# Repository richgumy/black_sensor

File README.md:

# Soft Surface Pressure Sensor using EIT
Black sensor is a project aimed at characterising carbon black silicone composites (and other piezoresistive conductive particle elastomer composites). This material can also be used as a pressure sensitive skin. The sensor system uses the principle of electrical impedance tomography (EIT) to reconstruct a resisitivty map of a flat sheet of piezoresisitive composite (characteristic limits of material yet to be determined. Such as min/max inter-electrode resisitvity and gauge factor) We will be only using DC as we are solely interested in the resisitive qualities of the composite for now, hence we're using electrical resistivity tomography (ERT). The sensor has been created that contains 4 major parts:

1) [ERT PCB hardware](/README.md#1---ert-pcb-hardware)
2) [ERT PCB firmware](/README.md#2---ert-pcb-firmware)
3) [Reconstruction software](/README.md#3---reconstruction-software)
4) [Sensor domain parts](/README.md#4---sensor-domain-parts)

A low cost PCB has been developed to capture the ERT data in reatime, which is streamed to a another computer to run a resistivity image reconstruction algorithm.

## 1 - ERT PCB hardware
The hardware driving the ERT sensor consist of either one custom ERT PCB or a MUX PCB used with an ESP32 development board and source measurement unit (SMU). All of the files to create the hardware are given as raw KiCad files. All of the component libraries may not exist so will need to made manually or imported.
[SMU PCB pinout here](/pcb-firmware/pcb_mux/README.md)
### 2.1 - ERT PCB
This board is for ERT data collection limited to sensor domains which have lower resisitances throughout the entirety of its intended use. The adjacent electrode resistance must not exceeed approx. 5 $k\Omega$.
#### Features:
- 5v USB power supply
- Onboard USB-UART programming
- Four 16:1 SPI MUXs
- Trimpot controlled current source
- Trimpot controlled voltage measurement gain
- 16 bit SPI ADC
- WiFi/BT capability
#### Future Features:
- Impedance measurements using network analyser
- Smaller PCB size
- Lower power MCU
### 2.2 - MUX PCB
This system consists of a SPI controlled 4:16 multiplexer (MUX) PCB used controlled with an ESP32 development board, PC and driven by a Keithley 2634b SMU and Keithley 2230G-30-1 DC power supply.
#### Features:
- Onboard USB-UART programming
- Four 16:1 SPI MUXs
- WiFi/BT capability
#### Future Features:
- Miniatruise and move all this system's functionality to the ERT PCB

## 2 - ERT PCB firmware
To run a test with the Cartesian force applicator see instructions in directory [here](pcb-firmware/pcb_mux/README.md)

### 2.1 - ERT PCB
The PCB firmware is all written in C for the ESP32-WROOM SoC connected to a custom 'ERT PCB'. The firmware applies an electrode pattern to the electrodes and sends measurement data via the USB UART serial connection.
The basic electrode drive process is:
1. Apply current to 2 electrodes
2. Measure voltage across 16 electrode pairs
3. Send voltage measurement data via serial
4. Iterate to next set of current electrodes.
5. Back to step 1.
#### Features:
- Drive modes: Standby, Calibrate, Adjacent
- Measurement averaging
- 16bit analog reading
#### Future Features:
- Bluetooth transmission of serial data
- More drive modes: Pseudo polar, PP-PP
- Nonense data checker (Throw error if data is very noisy or ADC saturated etc.)
- Speed up measurement rate from 8Hz to 40Hz

### 2.2 - MUX PCB - ESP32/PC
This is a more modular approach so that we are not limited by the ERT PCB's current source and power supply values. This system has five main components: A Keithley 2634b SMU, a MUX PCB, an ESP32 WROOM32 development board, a Keithley 2230G-30-1 DC power supply, and a piezoresistive sensor domain. The whole system is controlled via the PCB connected to the ESP32 and SMU over UART. 
The basic electrode drive process is:
1. Apply current to 2 electrodes
2. Measure voltage across 16 electrode pairs
3. Send voltage measurement data via serial
4. Iterate to next set of current electrodes.
5. Back to step 1.

These steps are done using a PC to send commands for switching the MUC PCB and query messages sent to the SMU to get voltage and current values.

#### Features:
- Simple serial control
- Voltage measurement time integration
- Nonense data checker (Throw error if SMU Isrc voltage saturating or DC power supply saturating)
- Logs the electrode resistance at beginning of cycle

#### Future Features:
- More drive modes: Pseudo polar, PP-PP
- Speed up measurement rate from 0.3Hz to ??Hz

## 3 - Reconstruction software
EIDORS was used as the library for image reconstruction using the data gathered from the PCB. A reference measurement is taken from the material on start-up of the reconstruction program. The reference measurement is compared to a current measurement for change in resisitvity (\Delta R) image reconstruction.

### Features:
- Reconstructs image in realtime using serial data.
- Save images for video generation
- See EIDORS documentation for an extensive feature list: http://eidors3d.sourceforge.net/index.shtml
- Timestamped FEM and measurement data exported to .pkl files.

### Future Features:
- Optimise reconstruction by porting all functionality to C++ or for use with a TPU/GPU.

## 4 - Sensor domain mechanical parts
The rest of the physical system consists of:
1. Composite material under test (MUT)
2. MUT holder
3. MUT electrodes
The material we are using is a carbon black nanoparticle silicone rubber composite, with customisable properties depending on the fabrication process. The MUT holder is a 3D printed part that provides an ideal platform for the material to be tested on. The MUT electrodes maintain a reliable connection between the MUT and the ERT PCB.
### Features:
- 100mm diameter pressure test area
- Easily customisable for other MUT sizes and MUT materials within measurement range.
### Future Features:
- Standard test domains and MUT holder/electrode configurations

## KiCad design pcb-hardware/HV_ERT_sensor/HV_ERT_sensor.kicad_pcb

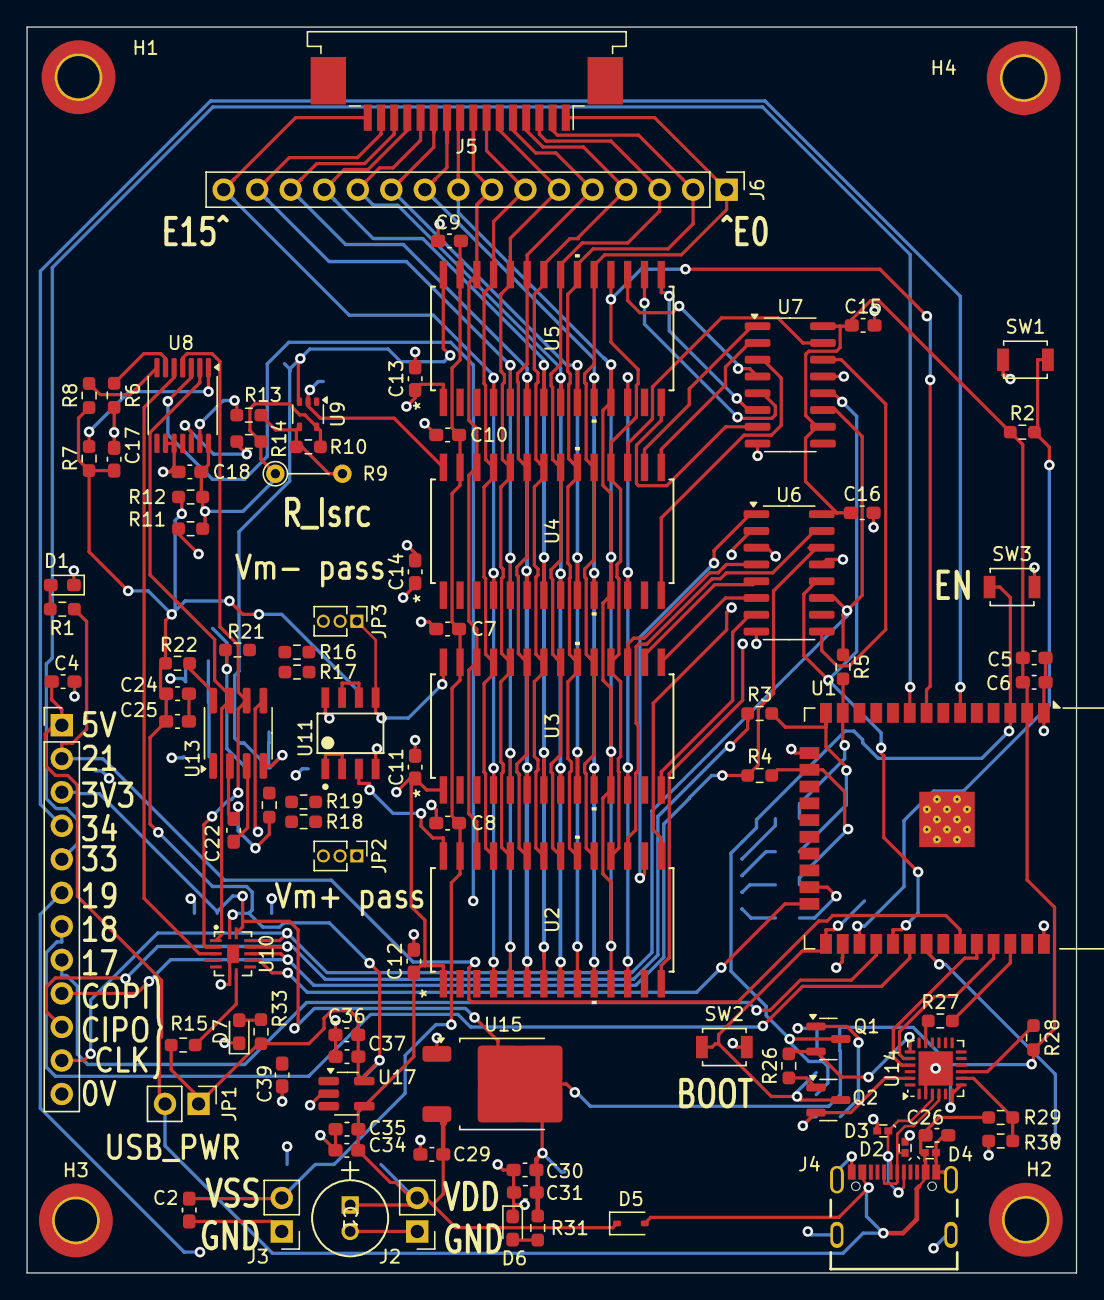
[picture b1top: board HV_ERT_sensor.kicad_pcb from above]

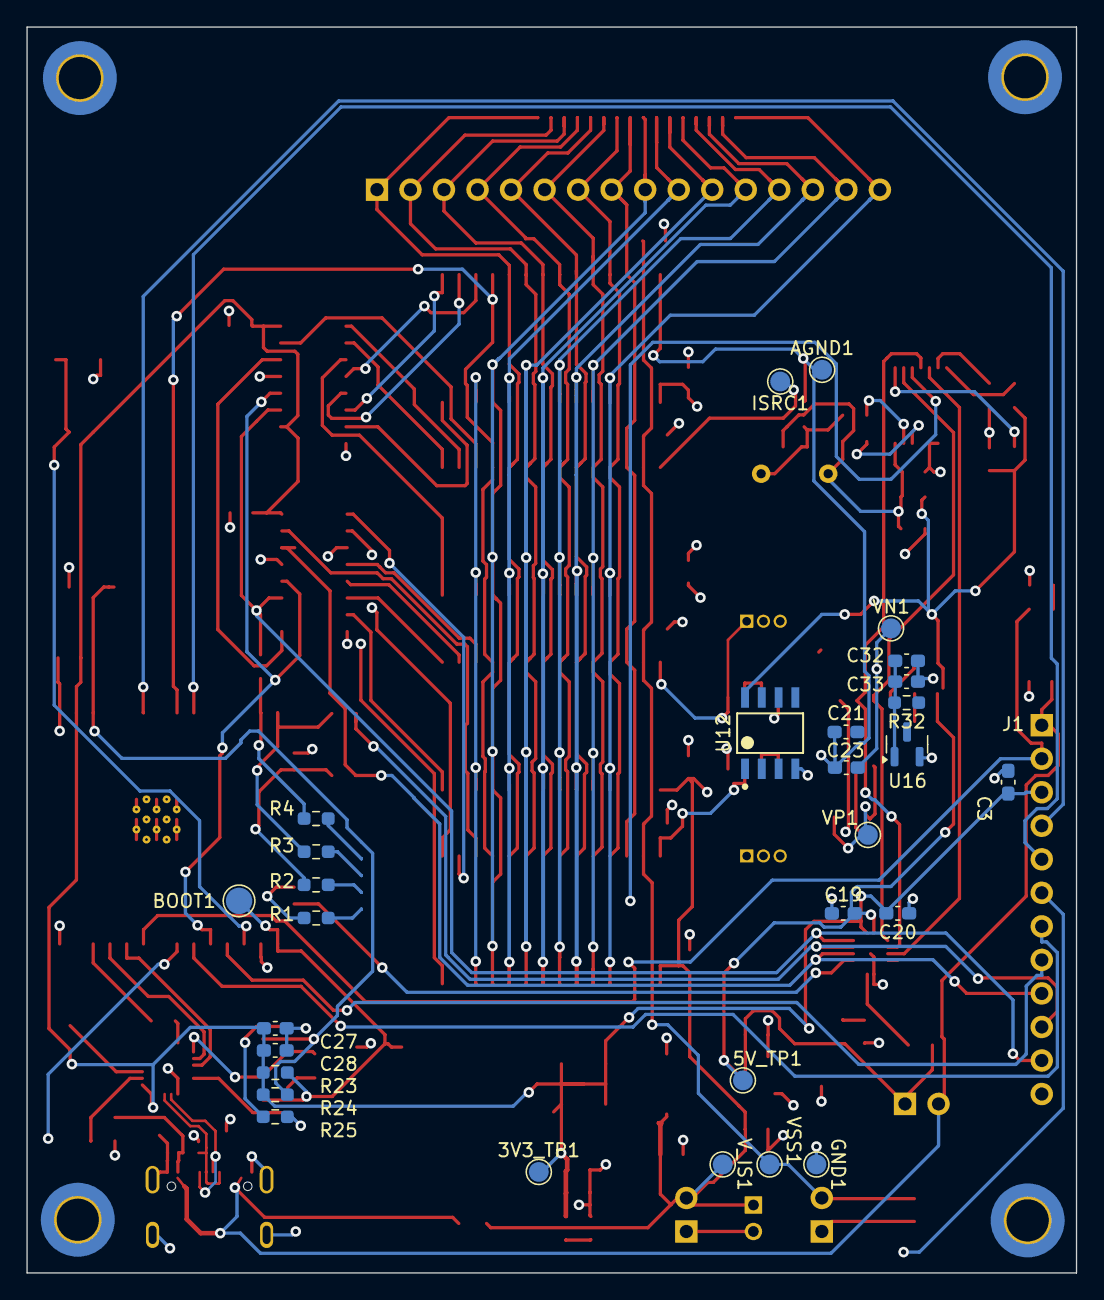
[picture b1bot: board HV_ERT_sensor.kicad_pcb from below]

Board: 4 copper layers, 79.5 x 94.4 mm, 127 parts (29 on the bottom side), 101 nets.

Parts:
3V3_TP1, 5V_TP1: TestPoint; TestPoint_Pad_D1.5mm
AGND1: TestPoint; TestPoint_Pad_D1.5mm
BOOT1: TP_s; TestPoint_Pad_D2.0mm
C1: C_Polarized; CAP_PAN_5X11_PAN
C2, C5, C24, C33, C37: 1u; C_0603_1608Metric_Pad1.08x0.95mm_HandSolder
C3, C4, C6, C7, C8, C9, C10, C11, C12, C13, C14, C15, C16, C17, C18, C19, C20, C25, C28, C30, C32, C35, C39: 100n; C_0603_1608Metric_Pad1.08x0.95mm_HandSolder
C21, C23: 1n; C_0603_1608Metric_Pad1.08x0.95mm_HandSolder
C22: 10n; C_0603_1608Metric_Pad1.08x0.95mm_HandSolder
C26, C29, C31: 10u; C_0603_1608Metric_Pad1.08x0.95mm_HandSolder
C27: 4u7; C_0603_1608Metric_Pad1.08x0.95mm_HandSolder
C34, C36: 470n; C_0603_1608Metric_Pad1.08x0.95mm_HandSolder
D1, D6, D7: 150060VS75000; LED_0603_1608Metric_Pad1.05x0.95mm_HandSolder
D2, D3, D4: UAD8C05L01; D_SOD-882
D5: BAT760-7; D_SOD-323
GND1: TestPoint; TestPoint_Pad_D1.5mm
H1, H2, H3, H4: MountingHole_Pad; MountingHole_3.2mm_M3_DIN965_Pad_TopBottom
ISRC1: TestPoint; TestPoint_Pad_D1.5mm
J1: Conn_01x12_Pin; PinHeader_1x12_P2.54mm_Vertical
J2, J3: Conn_01x02_Male; PinHeader_1x02_P2.54mm_Vertical
J4: USB_C_HEADER; GCT_USB4105-GF-A
J5: Conn_01x16; TE_1-84952-6_1x16-1MP_P1.0mm_Horizontal
J6: Conn_01x16; PinHeader_1x16_P2.54mm_Vertical
JP1: Jumper_2_Open; PinHeader_1x02_P2.54mm_Vertical
JP2, JP3: Jumper_3_Open; PinHeader_1x03_P1.27mm_Vertical
Q1, Q2: BC848; SOT-23
R1, R1#2, R2#2, R3#2, R4#2, R20, R21, R31: 100R; R_0603_1608Metric_Pad0.98x0.95mm_HandSolder
R2, R6, R8, R15, R23, R24, R25, R26, R28, R32: 10k; R_0603_1608Metric_Pad0.98x0.95mm_HandSolder
R3, R4, R5: 68R; R_0603_1608Metric_Pad0.98x0.95mm_HandSolder
R7, R11, R12, R13, R14, R22: 0R; R_0603_1608Metric_Pad0.98x0.95mm_HandSolder
R9: 0R; R_Axial_DIN0204_L3.6mm_D1.6mm_P5.08mm_Vertical
R10: 680R; R_0603_1608Metric_Pad0.98x0.95mm_HandSolder
R16, R18: 3k3 1%; R_0603_1608Metric_Pad0.98x0.95mm_HandSolder
R17, R19: 1k 1%; R_0603_1608Metric_Pad0.98x0.95mm_HandSolder
R27: 10K; R_0603_1608Metric_Pad0.98x0.95mm_HandSolder
R29: 22K; R_0603_1608Metric_Pad0.98x0.95mm_HandSolder
R30: 47K; R_0603_1608Metric_Pad0.98x0.95mm_HandSolder
R33: 200R; R_0603_1608Metric_Pad0.98x0.95mm_HandSolder
SW1: PTS636; SW_SPST_B3U-1000P
SW2, SW3: PTS636 SM50 SMTR LFS; SW_SPST_B3U-1000P
U1: ESP32-WROOM-32
U2, U3, U4, U5: DG406DYZ; SOIC28_7P60X18P10_INR-M
U6, U7: SN74HC595; SOIC-16_3.9x9.9mm_P1.27mm
U8: MCP41HV51-103E/ST; TSSOP-14_4.4x5mm_P0.65mm
U9: PSSI2021SAY; SOT-353_SC-70-5
U10: NTS0104BQ; DHVQFN14-2.5x3
U11, U12: OPA2991IDR; D0008A-MFG
U13: LTC1864; SOIC-8_3.9x4.9mm_P1.27mm
U14: CP2102N-A01-GQFN24; QFN-24-1EP_4x4mm_P0.5mm_EP2.6x2.6mm
U15: LD1086DT33TR; TO-252-2
U16: ADR5045BRTZ; SOT-23
U17: LDK715M50R_SOT23-5; SOT-23-5_HandSoldering
VN1: TestPoint; TestPoint_Pad_D1.5mm
VP1: TestPoint; TestPoint_Pad_D1.5mm
VSS1: TestPoint; TestPoint_Pad_D1.5mm
V_IS1: TestPoint; TestPoint_Pad_D1.5mm

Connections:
5V_USB: C4.2, C26.1, D4.1 (A1), D5.2 (A), J1.1, J4.A4_B9 (VBUS), J4.B4_A9 (VBUS), JP1.2 (B), R29.1
+3V3: 3V3_TP1.1, C3.2, C5.1, C6.1, C15.1, C16.1, C20.2, C27.1, C28.1, C30.2, C31.1, J1.3, R2.1, R23.1, R24.1, R28.2, R31.1, U1.2 (VDD), U6.10 (~SRCLR), U6.16 (VCC), U7.10 (~SRCLR), U7.16 (VCC), U10.14 (VCCB), U14.6 (VDD), U14.7 (REGIN), U15.2 (OUT)
+5V: 5V_TP1.1, C17.2, C19.2, C24.1, C25.2, C36.2, C37.1, JP1.1 (A), R7.1, R8.1, R12.1, R15.2, R22.2, R33.1, U10.1 (VCCA), U12.8 (V+), U17.5 (OUT)
/ADC_CS: U1.24 (IO2), U10.10 (B4)
/BOOT: BOOT1.1, Q2.3 (C), R23.2, SW2.1, U1.25 (IO0)
/DIGPOT_CS: U1.26 (IO4), U8.3 (*CS)
/EN: Q1.3 (C), R24.2, SW3.1, U1.3 (EN)
/IO15_SW: R2.2, SW1.2, U1.27 (IO16)
/IO17: J1.8, U1.28 (IO17)
/IO18: J1.7, U1.30 (IO18)
/IO19: J1.6, U1.31 (IO19)
/IO21_LED: J1.2, R1.1, U1.33 (IO21)
/IO33: J1.5, U1.9 (IO33)
/IO34: J1.4, U1.6 (IO34)
/Isrc: ISRC1.1, U4.28 (D), U9.2
/MTCLK: R2#2.1, R4.2, U1.16 (IO13)
/MTDI: R3.2, R3#2.1, U1.14 (IO12)
/MTDO: R1#2.1, U1.23 (IO15)
/MTMS: R4#2.1, R5.2, U1.13 (IO14)
/MUX_CS: U1.29 (IO5), U6.12 (RCLK), U7.12 (RCLK)
/MUX_EN: U1.8 (IO32), U2.18 (EN), U3.18 (EN), U4.18 (EN), U5.18 (EN)
/RXD: U1.35 (TXD0/IO1), U14.20 (RXD)
/SPICIPO: J1.10, R3.1, U10.12 (B2)
/SPICLK: J1.11, R5.1, U6.11 (SRCLK), U7.11 (SRCLK), U10.13 (B1)
/SPICOPI: J1.9, R4.1, U6.14 (SER), U10.11 (B3)
/TXD: U1.34 (RXD0/IO3), U14.21 (TXD)
/USB_DN: D2.1 (A1), J4.A7 (DN1), J4.B7 (DN2), U14.4 (D-)
/USB_DP: D3.1 (A1), J4.A6 (DP1), J4.B6 (DP2), U14.3 (D+)
/USB_SUSP: R27.2, U1.36 (IO22)
/Vmeas+: JP2.1 (A), U2.28 (D), U11.3 (IN1+)
/Vmeas-: JP3.1 (A), U3.28 (D), U11.5 (IN2+)
/eit_drv/ADC_CS5V: U10.5 (A4), U13.5 (CONV)
/eit_drv/R_IS1: C18.1, R9.1, R10.1, R11.2, R12.2, R14.1, U8.14 (V+), U9.5
/eit_drv/R_IS2: R9.2, R10.2, R13.2, U9.4
/eit_drv/SPICIPO5V: U8.4 (SDI), U10.3 (A2), U13.6 (SDO)
/eit_drv/SPICLK5V: U8.2 (SCK), U10.2 (A1), U13.7 (SCK)
/eit_drv/SPICOPI5V: U8.5 (SDO), U10.4 (A3)
/eit_drv/Vmeas+_ADC: JP2.2 (C), R20.1
/eit_drv/Vmeas+_Op: JP2.3 (B), U12.1 (OUT1), U12.2 (IN1-)
/eit_drv/Vmeas-_ADC: JP3.2 (C), R21.1
/eit_drv/Vmeas-_Op: JP3.3 (B), U12.6 (IN2-), U12.7 (OUT2)
/mux_4-16/S0_A: U2.17 (A0), U6.15 (QA)
/mux_4-16/S0_B: U3.17 (A0), U6.4 (QE)
/mux_4-16/S1_A: U2.16 (A1), U6.1 (QB)
/mux_4-16/S1_B: U3.16 (A1), U6.5 (QF)
/mux_4-16/S2_A: U2.15 (A2), U6.2 (QC)
/mux_4-16/S2_B: U3.15 (A2), U6.6 (QG)
/mux_4-16/S3_A: U2.14 (A3), U6.3 (QD)
/mux_4-16/S3_B: U3.14 (A3), U6.7 (QH)
/mux_4-16/S4_A: U4.17 (A0), U7.15 (QA)
/mux_4-16/S4_B: U5.17 (A0), U7.4 (QE)
/mux_4-16/S5_A: U4.16 (A1), U7.1 (QB)
/mux_4-16/S5_B: U5.16 (A1), U7.5 (QF)
/mux_4-16/S6_A: U4.15 (A2), U7.2 (QC)
/mux_4-16/S6_B: U5.15 (A2), U7.6 (QG)
/mux_4-16/S7_A: U4.14 (A3), U7.3 (QD)
/mux_4-16/S7_B: U5.14 (A3), U7.7 (QH)
/power/5V_REF: C32.2, C33.1, R32.2, U16.1 (V+)
/usb2uart/DTR: Q2.2 (E), R25.2, U14.23 (DTR)
/usb2uart/RTS: Q1.2 (E), R26.2, U14.19 (RTS)
/usb2uart/VBUS_UART: R29.2, R30.1, U14.8 (VBUS)
E0: J5.1, J6.1, U2.19 (S1), U3.19 (S1), U4.19 (S1), U5.19 (S1)
E1: J5.2, J6.2, U2.20 (S2), U3.20 (S2), U4.20 (S2), U5.20 (S2)
E2: J5.3, J6.3, U2.21 (S3), U3.21 (S3), U4.21 (S3), U5.21 (S3)
E3: J5.4, J6.4, U2.22 (S4), U3.22 (S4), U4.22 (S4), U5.22 (S4)
E4: J5.5, J6.5, U2.23 (S5), U3.23 (S5), U4.23 (S5), U5.23 (S5)
E5: J5.6, J6.6, U2.24 (S6), U3.24 (S6), U4.24 (S6), U5.24 (S6)
E6: J5.7, J6.7, U2.25 (S7), U3.25 (S7), U4.25 (S7), U5.25 (S7)
E7: J5.8, J6.8, U2.26 (S8), U3.26 (S8), U4.26 (S8), U5.26 (S8)
E8: J5.9, J6.9, U2.11 (S9), U3.11 (S9), U4.11 (S9), U5.11 (S9)
E9: J5.10, J6.10, U2.10 (S10), U3.10 (S10), U4.10 (S10), U5.10 (S10)
E10: J5.11, J6.11, U2.9 (S11), U3.9 (S11), U4.9 (S11), U5.9 (S11)
E11: J5.12, J6.12, U2.8 (S12), U3.8 (S12), U4.8 (S12), U5.8 (S12)
E12: J5.13, J6.13, U2.7 (S13), U3.7 (S13), U4.7 (S13), U5.7 (S13)
E13: J5.14, J6.14, U2.6 (S14), U3.6 (S14), U4.6 (S14), U5.6 (S14)
E14: J5.15, J6.15, U2.5 (S15), U3.5 (S15), U4.5 (S15), U5.5 (S15)
E15: J5.16, J6.16, U2.4 (S16), U3.4 (S16), U4.4 (S16), U5.4 (S16)
GND: AGND1.1, C1.2, C2.2, C3.1, C4.1, C5.2, C6.2, C7.2, C8.2, C9.2, C10.2, C11.2, C12.2, C13.2, C14.2, C15.2, C16.2, C17.1, C18.2, C19.1, C20.1, C21.1, C23.1, C24.2, C25.1, C26.2, C27.2, C28.2, C29.2, C30.1, C31.2, C32.1, C33.2, C34.2, C35.2, C36.1, C37.2, C39.2, D1.1 (K), D2.2 (A2), D3.2 (A2), D4.2 (A2), D6.1 (K), D7.1 (K), GND1.1, H1.1, H2.1, H3.1, H4.1, J1.12, J2.1, J3.1, J4.A1_B12 (GND), J4.B1_A12 (GND), J4.S1 (SHELL_GND), J4.S2 (SHELL_GND), J4.S3 (SHELL_GND), J4.S4 (SHELL_GND), R6.2, R17.1, R19.1, R30.2, SW1.1, SW2.2, SW3.2, U1.1 (GND), U1.15 (GND), U1.38 (GND), U1.39 (GND), U2.12 (GND), U3.12 (GND), U4.12 (GND), U5.12 (GND), U5.28 (D), U6.8 (GND), U6.13 (~OE), U7.8 (GND), U7.13 (~OE), U8.9 (DGND), U8.10 (V-), U9.3 (GND), U10.7 (GND), U11.4 (V-), U12.4 (V-), U13.4 (GND), U14.2 (GND), U14.25 (GND), U15.1 (ADJ/GND), U16.2 (V-), U17.2 (GND)
unnamed: D1.2 (A), R1.2
unnamed: D6.2 (A), R31.2
unnamed: D7.2 (A), R33.2
unnamed: Q1.1 (B), R25.1
unnamed: Q2.1 (B), R26.1
unnamed: U6.9 (QH'), U7.14 (SER)
unnamed: R8.2, U8.7 (*SHDN)
unnamed: R6.1, U8.6 (*WLAT)
unnamed: R13.1, U8.13 (P0A)
unnamed: R14.2, U8.12 (P0W)
unnamed: R7.2, U8.1 (VL)
unnamed: R15.1, U10.8 (OE)
unnamed: R18.2, U11.1 (OUT1), U11.2 (IN1-)
unnamed: R16.2, U11.6 (IN2-), U11.7 (OUT2)
unnamed: R18.1, R19.2, U12.3 (IN1+)
unnamed: R16.1, R17.2, U12.5 (IN2+)
unnamed: C21.2, C22.2, R20.2, U13.2 (IN+), VP1.1
unnamed: C22.1, C23.2, R21.2, U13.3 (IN-), VN1.1
unnamed: R22.1, U13.8 (VCC)
unnamed: R27.1, U14.17 (SUSPEND)
unnamed: R28.1, U14.9 (~RSTb)
VDD: C1.1, C11.1, C12.1, C13.1, C14.1, C29.1, C34.1, C35.1, D5.1 (K), J2.2, R11.1, R32.1, U2.1 (V+), U3.1 (V+), U4.1 (V+), U5.1 (V+), U11.8 (V+), U15.3 (IN), U17.4 (IN), V_IS1.1
VSS: C2.1, C7.1, C8.1, C9.1, C10.1, J3.2, U2.27 (V-), U3.27 (V-), U4.27 (V-), U5.27 (V-), VSS1.1

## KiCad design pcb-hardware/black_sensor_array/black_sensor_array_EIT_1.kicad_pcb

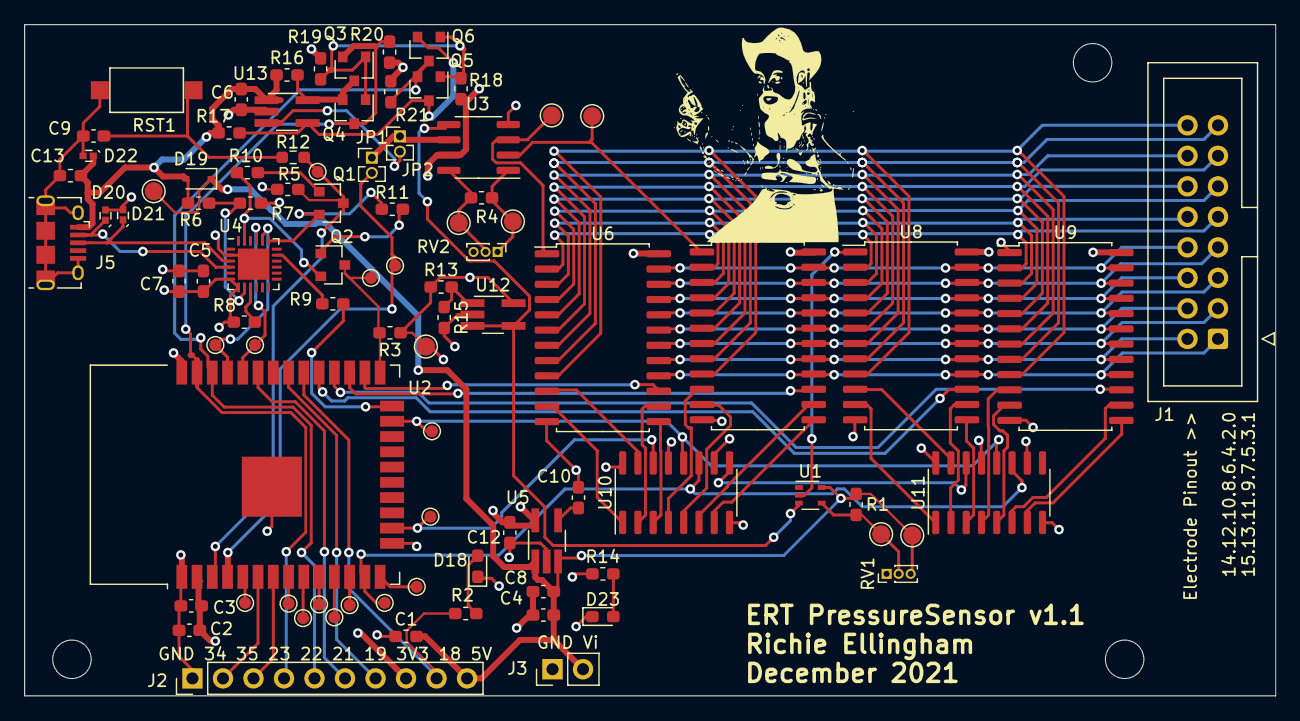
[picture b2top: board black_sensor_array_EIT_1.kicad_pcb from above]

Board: 4 copper layers, 104.1 x 55.9 mm, 93 parts (0 on the bottom side), 90 nets.

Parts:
C1: 100n; C_0603_1608Metric_Pad1.05x0.95mm_HandSolder
C2, C6, C7, C9: 100n; C_0603_1608Metric_Pad1.08x0.95mm_HandSolder
C3, C4, C5: 10u; C_0603_1608Metric_Pad1.08x0.95mm_HandSolder
C8: 1u; C_0603_1608Metric_Pad1.08x0.95mm_HandSolder
C10: 10n; C_0603_1608Metric_Pad1.08x0.95mm_HandSolder
C12: 2.2u; C_0603_1608Metric_Pad1.08x0.95mm_HandSolder
C13: 10u; C_0603_1608Metric_Pad1.05x0.95mm_HandSolder
D18, D23: 150060VS75000; LED_0603_1608Metric_Pad1.05x0.95mm_HandSolder
D19: BAT760-7; D_SOD-323
D20, D21, D22: UAD8C05L01; D_SOD-882
H1, H2, H3: MountingHole; MountingHole_3.2mm_M3
J1: Conn_02x8; IDC-Header_2x08_P2.54mm_Vertical
J2: Conn_01x10_Male; PinHeader_1x10_P2.54mm_Vertical
J3: Conn_01x02_Male; PinHeader_1x02_P2.54mm_Vertical
J5: USB_B_Micro; USB_Micro-B_Amphenol_10118194_Horizontal
JP1, JP2: Jumper; PinHeader_1x02_P1.27mm_Vertical
Q1, Q2, Q3, Q4, Q5, Q6: BC848; SOT-23
R1: 120K; R_0603_1608Metric_Pad1.05x0.95mm_HandSolder
R2, R14: 100R; R_0603_1608Metric_Pad1.05x0.95mm_HandSolder
R3, R5, R8, R10, R11, R13, R15, R16, R17, R18, R19, R20, R21: 10k; R_0603_1608Metric_Pad1.05x0.95mm_HandSolder
R4, R7: 47K; R_0603_1608Metric_Pad1.05x0.95mm_HandSolder
R6: 22K; R_0603_1608Metric_Pad1.05x0.95mm_HandSolder
R9: 10K; R_0603_1608Metric_Pad1.05x0.95mm_HandSolder
R12: 100R; R_0603_1608Metric_Pad0.98x0.95mm_HandSolder
RST1: PTS636 SM50 SMTR LFS; SW_SPST_CK_RS282G05A3
RV1, RV2: R_POT_TRIM; PinHeader_1x03_P1.00mm_Vertical
TP1, TP2, TP8, TP9, TP14, TP15, TP18, TP23: TestPoint; TestPoint_Pad_D1.5mm
TP3, TP4, TP5, TP6, TP7, TP10, TP11, TP12, TP13, TP16, TP17, TP19, TP20, TP21, TP22: TP_s; TestPoint_Pad_D1.0mm
U1: PSSI2021SAY; SOT-353_SC-70-5
U2: ESP32-WROOM-32
U3: INA126; SOIC-8_3.9x4.9mm_P1.27mm
U4: CP2102N-A01-GQFN24; QFN-24-1EP_4x4mm_P0.5mm_EP2.6x2.6mm
U5: CAT6219−330TDGT3; TSOT-23-5_HandSoldering
U6, U7, U8, U9: CD74HC4067M; SOIC-24W_7.5x15.4mm_P1.27mm
U10, U11: SN74HC595; SOIC-16_3.9x9.9mm_P1.27mm
U12: MCP6006UT-E_OT; TSOT-23-5_HandSoldering
U13: MCP3221A7T-E_OT; TSOT-23-5_HandSoldering

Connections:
+3V3: C2.1, C3.1, C5.1, C7.1, C12.1, J2.8, R3.1, R5.1, R8.2, R13.1, R14.1, R18.1, R19.1, R20.1, R21.1, TP23.1, U2.2, U3.7, U4.6, U4.7, U5.5, U6.24, U7.24, U8.24, U9.24, U10.10, U10.16, U11.10, U11.16, U12.5
/3v3_PU: Q3.1, Q4.1, Q5.1, Q6.1, R18.2, R19.2
/5VBUS: C6.1, C13.1, D19.2, D22.1, J5.1, R6.1, R16.1, R17.1, U13.1
/5V_USB: C1.2, C4.2, C8.1, D19.1, J2.10, J3.2, R1.1, RV1.3, TP1.1, TP18.1, U1.5, U5.1, U5.3
/ADC_jump: JP1.1, JP2.1, U3.6
/ADC_jump_ex: JP2.2, U13.3
/ADC_jump_int: JP1.2, TP16.1, U2.4
/DTR: Q2.2, R10.2, U4.23
/DTR*: Q2.3, R3.2, TP22.1, U2.25
/E0x: J1.16, U6.9, U7.9, U8.9, U9.9
/E1x: J1.15, U6.8, U7.8, U8.8, U9.8
/E2x: J1.14, U6.7, U7.7, U8.7, U9.7
/E3x: J1.13, U6.6, U7.6, U8.6, U9.6
/E4x: J1.12, U6.5, U7.5, U8.5, U9.5
/E5x: J1.11, U6.4, U7.4, U8.4, U9.4
/E6x: J1.10, U6.3, U7.3, U8.3, U9.3
/E7x: J1.9, U6.2, U7.2, U8.2, U9.2
/E8x: J1.8, U6.23, U7.23, U8.23, U9.23
/E9x: J1.7, U6.22, U7.22, U8.22, U9.22
/E10x: J1.6, U6.21, U7.21, U8.21, U9.21
/E11x: J1.5, U6.20, U7.20, U8.20, U9.20
/E12x: J1.4, U6.19, U7.19, U8.19, U9.19
/E13x: J1.3, U6.18, U7.18, U8.18, U9.18
/E14x: J1.2, U6.17, U7.17, U8.17, U9.17
/E15x: J1.1, U6.16, U7.16, U8.16, U9.16
/EN_GND: U2.28, U9.15
/EN_Isrc: U2.29, U8.15
/EN_Vmeas+: U2.26, U6.15
/EN_Vmeas-: U2.27, U7.15
/HSPICLK: TP12.1, U2.13, U10.11, U11.11
/HSPICS0: TP13.1, U2.23, U10.12, U11.12
/HSPIMISO: TP10.1, U2.14
/HSPIMOSI: TP11.1, U2.16, U10.14
/IO18_LED: J2.9, R2.1, U2.30
/IO19: J2.7, U2.31
/IO21: J2.6, U2.33
/IO34: J2.2, U2.6
/IO35: J2.3, U2.7
/Isrc: U1.2, U8.1
/MUX_16to4/S0_A: U6.10, U10.15
/MUX_16to4/S0_B: U7.10, U10.4
/MUX_16to4/S1_A: U6.11, U10.1
/MUX_16to4/S1_B: U7.11, U10.5
/MUX_16to4/S2_A: U6.14, U10.2
/MUX_16to4/S2_B: U7.14, U10.6
/MUX_16to4/S3_A: U6.13, U10.3
/MUX_16to4/S3_B: U7.13, U10.7
/MUX_16to4/S4_A: U8.10, U11.15
/MUX_16to4/S4_B: U9.10, U11.4
/MUX_16to4/S5_A: U8.11, U11.1
/MUX_16to4/S5_B: U9.11, U11.5
/MUX_16to4/S6_A: U8.14, U11.2
/MUX_16to4/S6_B: U9.14, U11.6
/MUX_16to4/S7_A: U8.13, U11.3
/MUX_16to4/S7_B: U9.13, U11.7
/RTS: Q1.2, R11.2, U4.19
/RTS*: Q1.3, R5.2, R12.1, TP21.1, U2.3
/RXD: TP19.1, U2.35, U4.20
/SCL_ADC: Q3.3, Q4.2, R16.2, U13.5
/SCL_ADC_3V3: J2.4, Q3.2, Q4.3, R20.2, U2.37
/SDA_ADC: Q5.3, Q6.2, R17.2, U13.4
/SDA_ADC_3V3: J2.5, Q5.2, Q6.3, R21.2, U2.36
/TXD: TP20.1, U2.34, U4.21
/USB_DN: D20.1, J5.2, U4.4
/USB_DP: D21.1, J5.3, U4.3
/USB_SUSP: R9.2, U2.24
/VBUS_UART: R6.2, R7.1, U4.8
/V_GND: U1.3, U3.5, U12.3, U12.4
/Vmeas+: TP8.1, U3.3, U6.1
/Vmeas-: TP9.1, U3.2, U7.1
GND: C1.1, C2.2, C3.2, C4.1, C5.2, C6.2, C7.2, C8.2, C9.2, C10.2, C12.2, C13.2, D18.1, D20.2, D21.2, D22.2, D23.1, J2.1, J3.1, J5.5, J5.6, R7.2, R15.2, RST1.2, U2.1, U2.15, U2.38, U2.39, U3.4, U4.2, U4.25, U5.2, U6.12, U7.12, U8.12, U9.1, U9.12, U10.8, U10.13, U11.8, U11.13, U12.2, U13.2
unnamed: C9.1, R12.2, RST1.1
unnamed: C10.1, U5.4
unnamed: D18.2, R2.2
unnamed: D23.2, R14.2
unnamed: Q1.1, R10.1
unnamed: Q2.1, R11.1
unnamed: R1.2, RV1.2, TP2.1, U1.4
unnamed: R4.1, RV2.1, TP14.1, U3.1
unnamed: R4.2, RV2.2, TP15.1, U3.8
unnamed: R8.1, U4.9
unnamed: R9.1, U4.17
unnamed: R13.2, R15.1, U12.1
unnamed: TP3.1, U2.10
unnamed: TP4.1, U2.11
unnamed: TP5.1, U2.12
unnamed: TP6.1, U2.8
unnamed: TP7.1, U2.9
unnamed: TP17.1, U2.5
unnamed: U10.9, U11.14

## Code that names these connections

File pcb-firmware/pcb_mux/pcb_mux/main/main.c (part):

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#define SW_2 15

// MUX
#define MUX_EN 32
#define MUX_CS_PIN 5

#define GPIO_OUTPUT_PIN_SEL  ((1ULL<<LED) | (1ULL<<MUX_EN))
#define GPIO_INPUT_PIN_SEL  ((1ULL<<SW_1) | (1ULL<<SW_2))

// ADC
#define ADC_CS_PIN 27
#define N_ADC_SAMPLES 1         // set ADC averaging buffer size

// Digipot
#define DIGPOT_CS 4

// Electrodes
static int8_t cycle_dir = 1; // Increment through electrode values (0 is decrement)
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
uint32_t conv_adc_readingLTC1864L(uint8_t data[]) {
    // Converts arbitrary analogue unit to readable mV value
    // uint32_t conv_offset = 0;//32533; // Calibrate for each board (i.e. V_GND)
    // uint32_t conv_scale = 65536;
    uint32_t conv_data = 0;

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{
    uint32_t spi_read = 0;
    uint32_t spi_read_avg = 0;
    // send_spi_cmd(spi_read_ADC, ADC_CS_PIN); // Discard ADC reading from previous cycle
    for (int i = 0; i < N_ADC_SAMPLES; i++) {
        send_spi_cmd(spi_read_ADC, ADC_CS_PIN); // Send SPI cmd to read ADC and store value in 'spi_read_ADC'
        spi_read = conv_adc_readingLTC1864L(spi_read_ADC);
        spi_read_avg += spi_read;
    }
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
    //Configure GPIO
    setup_all_gpio();
    gpio_set_level(MUX_EN, 1);

    ////// UART SPECIFIC CODE ////
    uart_config_t uart_config = {
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                v_read.vn_elec = vn_elec;

                 // Send SPI mux cmd
                send_spi_cmd(elec_index, MUX_CS_PIN);
           
                // ADC SPI read
                int32_t spi_read_avg = (int32_t)read_ADC(spi_read_ADC_buf);
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
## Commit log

2021-07-06 First commit adding code for a cycling through 3 pairs of electrodes, reading their voltage values via the nano's ADC and converting this to a resistance value.
2021-07-06 Added readme
2021-09-10 Added a program which gives the creates material square domain with surrounding electrodes. Finds the electric field for a dipole (current source of two electrodes) and working on creating equipotent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
2021-11-23 added functioning mux changing code for ESP32 based board and 4 muxes
2021-11-23 generalised readme
2021-11-25 calibration sequence added
2022-01-12 Fixing SPI crash with error
2022-01-12 fixed SPI crash bug by adding memset for bus_config...
2022-01-12 fixed ADJACENT electrode drive pattern bug
2022-01-25 added I2C ADC
2022-01-25 I2C ADC teething issues
2022-01-31 Added 24bit ADC SPI reading capability for LTC2400CS8 IC
2022-02-02 works using LT2400 ADC but sampling is slow
2022-02-04 added EIDORS live serial interpreter to give real time image reconstruction
2022-02-14 increased refresh rate of data collection and hence increased rate of reconstructions
2022-02-17 create array of solved images for .gif creation
2022-03-08 Added updated EIDORS files for use with Octave. Sped up ERT data acquisition
2022-03-09 Updated Readme
    More comprehensive breakdown of each part of the sensor system
2022-03-09 Testing link
2022-03-09 test link 2
2022-03-09 link3
2022-03-09 lnk4
2022-03-09 file clean up and categorisation
2022-03-09 img1
2022-03-09 updated media
2022-03-09 updated figs
2022-03-09 fig resize
2022-03-09 figs in html frmt
2022-03-09 more file sorting
2022-03-09 ert_firmware file restructure
2022-03-09 code block
2022-03-09 gramr
2022-03-10 Fixed bugs in: ert_serial_construct.m = not gathering measurement 'vh' data correctly. main.c = size of RX buffer too large, likely overflow occuring
2022-03-11 Speed up ERT pattern drive to 300us per -> read per whole cycle = 300*16*16*No_SAMPLES(eg=4) = 310ms. Hold colour bar more constant in scale (not completely though hmmm)
2022-03-22 Changed to C++ for future coding with classes and have created SPI driver which doesn't work.. yet. Code is speed optimised gathering all measurement data in <100ms
2022-03-22 Compatible with matlab - functionality (e.g. flush(ert_serial) function) unchecked with Octave. Doesn't crash when given invalid reconstruction data sets data to zero instead.
2022-03-22 file clean
2022-03-22 rename dir
2022-03-22 restructure
2022-03-23 wee python script for gathering serial data and plonking into a csv
2022-03-23 timestamps all data
2022-03-23 added example test .csv file
2022-03-23 update max sample rate
2022-03-23 title change
2022-07-08 added new code to analyse noise
2022-07-08 calibrated for ERT V1.2 with no virtual ground
2022-07-08 working on noise analysis code NOT COMPLETE. Also tidied up firmware to measure to mV with 1 d.p.
2022-07-11 fixed noise stats code, thanks Chris C
2022-07-19 updated firmware.
2022-08-18 branch test
2022-08-18 reset and restore of all files
2022-10-06 added simplified_ert_firmware program which uses less modular code but works more reliably than ert_firmware
2022-10-17 added untested calibration code for ERT PCB v1.2
2023-05-04 adding pcb_mux code
2023-06-13 haven't git pushed in a while. Added stable pcb_mux for esp32 dev board, before altering code to make compatible with esp32-s3 and c3
2023-06-14 Update README.md
    ESP-C3 compatibility deprecated.
2023-06-19 updated pc_mux GPIO and readme to give pinouts
2023-06-19 added pic
2023-06-19 added SW flow diagram
2023-07-02 added eit_reader.py which controls ERT data collection
2023-07-02 added code to report some key data points of a generated eit data file
2023-07-03 added non-functional force gathering code
2023-07-05 pickling of all experimental data done! Force measurements functional and written to CSV. ++
2023-07-17 made get_force module concept and attempting multiprocessing
2023-07-18 integrating pos measurment logging
2023-07-19 now loggin positions and saving to csv and pkl files
2023-07-19 Automated testing first trial actually functional making. Added strain, hold time, and push speed to eitf_frame data.
2023-07-20 eit voltage data should always be a multiple of 16^2 now and csv+pkl file will save before reading inter electrode resistance
2023-07-20 num_elecs defined as global now
2023-07-20 added in line parameter post_cal_t_relax = 240(secs) for post mesh bed leveling calibration wait time
2023-07-23 Updated init for eitf_dataframe vars. Finish point for eit_cfa_reader now at home_offset circle. Changed eit_cfa_checker but still doesn't work with # eit cycles larger than 16.
2023-07-26 fixed issue with using a pd array instead of np array with reshaping in the get_inter_elec_res() function
2023-07-28 made reshaped voltage data float format
2023-08-01 added file name to unstable electrode plot
2023-08-26 new eit_cfa_reader.py references x,y,z values from zero. batch_run.sh runs a series of pushes at different strains
2023-08-26 added filepath var
2023-10-02 added performance metric notebook and noise analysis notebook code
2023-10-02 Create performance_metrics.md
    wee descr of dir
2023-10-02 readme for performance metrics
2023-10-02 rm readme old
2023-10-16 updated the plot_fem/_f scales to be adjustable
2023-12-10 Add function to be used with the PyMesh docker for mesh 'blob' separation
2023-12-10 Added comments to DOCKER_fe...
2023-12-10 backing up .ipynb files
2024-01-14 Update README.md
    added load order image
2024-04-16 updated to medium voltage ERT hardware still WIP
2024-04-16 move files
2024-05-27 code for gathering ERT PCB v1.3 data concurrrently with force and position data.
2024-05-27 code for streaming live raw ERT PCB data into a CSV file
2024-05-28 fixed max-voltage bug
2024-05-29 added error checking code
2024-06-01 works but only when I have time.sleep(0.5) during ERT cycle. Might be requesting data faster than the PCB can give? Also the serial line is very error prone. Might need to fix this on the ESP side!
2024-06-02 fixed accidentally deleted line
2024-06-27 added minimal code for max data acquisistion
2024-06-27 added firmware for super fast data acquisistion.
2024-10-22 Physics informed NN tutorial.
2024-10-22 try to train on non-linear relationship
2024-10-23 Created a naive PINN for a viscoelastic stress response. Next step is to make one that takes into account input strain!
